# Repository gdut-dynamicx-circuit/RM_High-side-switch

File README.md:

# RM_High-side switch

&nbsp;&nbsp;&nbsp;&nbsp;

[English](./README.md)/中文

***

### 简介

&nbsp;&nbsp;&nbsp;&nbsp;本项目的开发目的是为了实现了电位控制电流。本项目基于lm5060芯片，实现了控制大电流开关的功能。

***

### 开发工具

+ EDA工具：KiCAD 7.0 

***

### 目录结构

+ circuit：基于KiCAD的原理图及PCB设计

+ docs：README相关的图片及文档

**注意：生产制造相关的Gerber、BOM、POS文件及程序固件均在仓库的Release中发布**

***

### 电路设计

#### 原理图设计要点

&nbsp;&nbsp;&nbsp;&nbsp;高侧开关的设计：通过三极管的共射放大电路，实现电位控制Nmos管的导通。在lm5060后面还接入一个可以放电源正负极反接作用的电路。在lm5060的GATE的引脚处串联了一个电阻再反并一个二极管和实现电源快开慢关的作用。

#### PCB布局布线要点

1. VIN旁路电容器靠近引脚VIN.
2. 计时器电容器靠近针脚TIMER.
3. MOS管处pcb打孔确保正反面导通

***

**组织：DynamicX <br>
维护人：陈晓根, 2383725658@qq.com**

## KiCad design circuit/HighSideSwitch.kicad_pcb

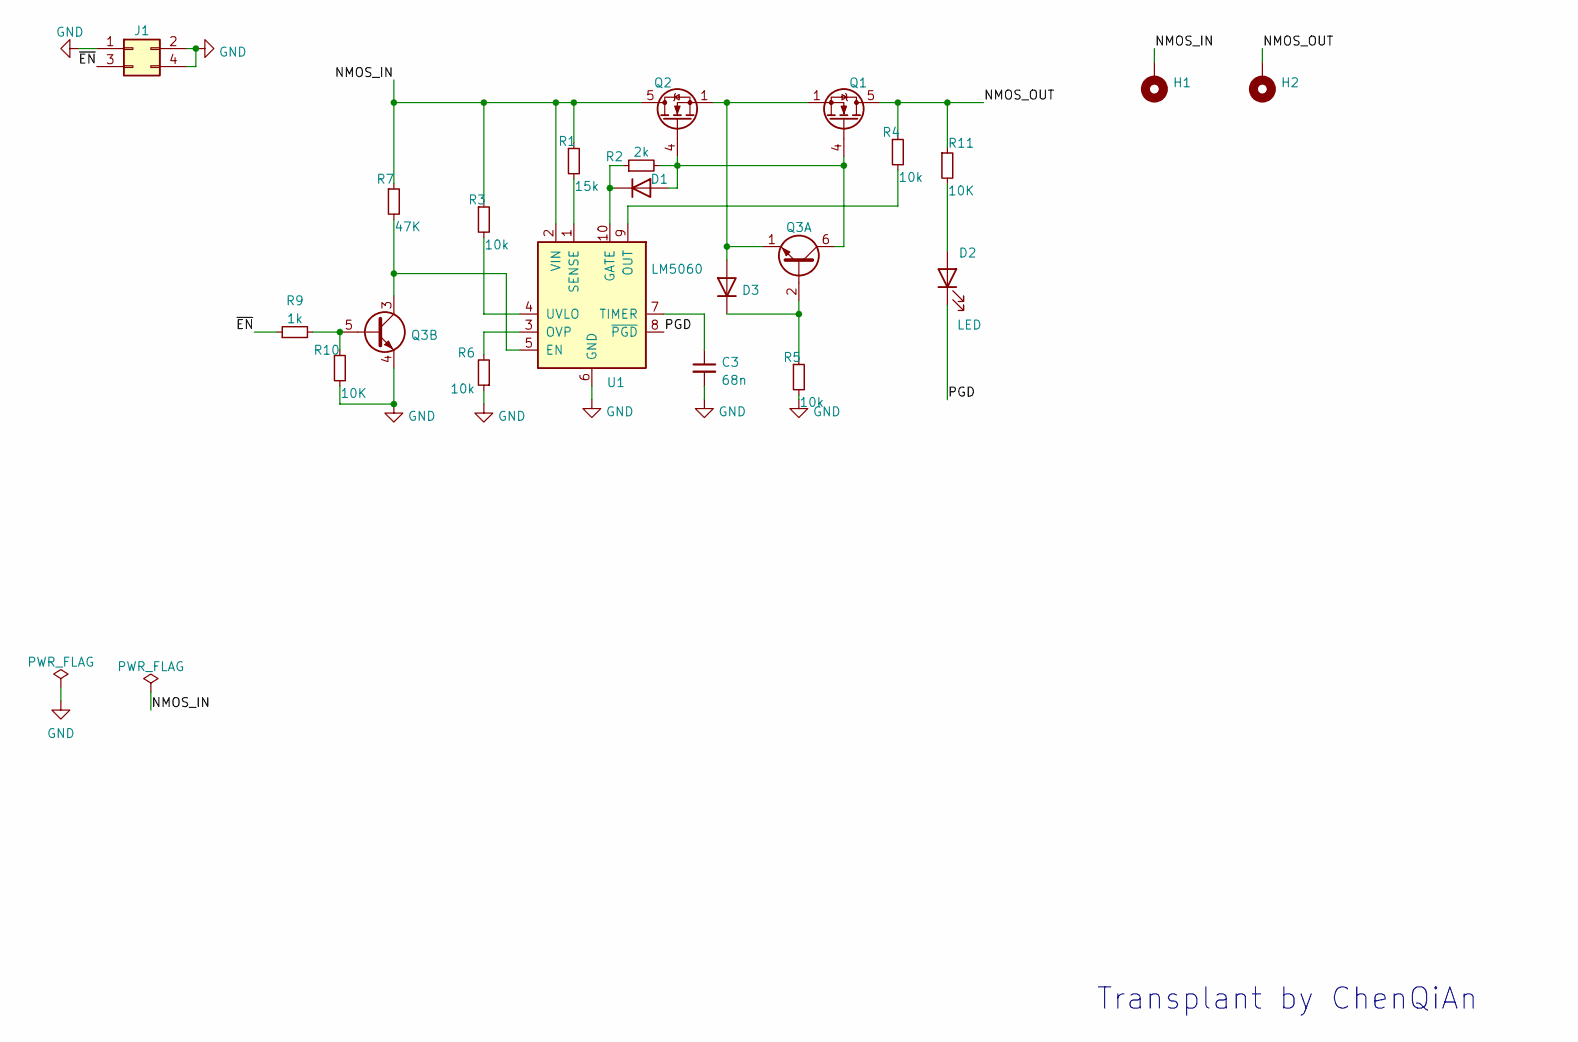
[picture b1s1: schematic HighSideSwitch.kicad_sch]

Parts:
C3: 68n; C_0402_1005Metric
D1, D3: 1N4001; D_SOD-323
D2: LED; LED_0603_1608Metric
H1, H2: MountingHole_Pad; MountingHole_3.2mm_M3_Pad_Via
J1: Conn_02x02_Odd_Even; PinHeader_2x02_P1.27mm_Vertical_SMD
Q1, Q2: CSD18540Q5B; TDSON-8-1
Q3: Q_Dual_NPN_NPN_E1B1C2E2B2C1; SOT-363_SC-70-6
R1: 15k; R_0402_1005Metric
R2: 2k; R_0402_1005Metric
R3, R4, R5, R6: 10k; R_0402_1005Metric
R7: 47K; R_0402_1005Metric
R9: 1k; R_0402_1005Metric
R10, R11: 10K; R_0402_1005Metric
U1: LM5060; MSOP-10_3x3mm_P0.5mm

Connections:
/NMOS_IN: H1.1, Q2.5 (D), R1.1, R3.1, R7.1, U1.2 (VIN)
/NMOS_OUT: H2.1, Q1.5 (D), R4.1, R11.1
/PGD: D2.1 (K), U1.8 (~PGD)
/~EN: J1.3, R9.1
GND: C3.2, J1.1, J1.2, J1.4, Q3.4 (E2), R5.2, R6.1, R10.2, U1.6 (GND)
unnamed: C3.1, U1.7 (TIMER)
unnamed: D1.1 (K), R2.1, U1.10 (GATE)
unnamed: D1.2 (A), Q1.4 (G), Q2.4 (G), Q3.6 (C1), R2.2
unnamed: D2.2 (A), R11.2
unnamed: D3.1 (K), Q3.2 (B1), R5.1
unnamed: D3.2 (A), Q1.1 (S), Q1.2 (S), Q1.3 (S), Q2.1 (S), Q2.2 (S), Q2.3 (S), Q3.1 (E1)
unnamed: Q3.3 (C2), R7.2, U1.5 (EN)
unnamed: Q3.5 (B2), R9.2, R10.1
unnamed: R1.2, U1.1 (SENSE)
unnamed: R3.2, U1.4 (UVLO)
unnamed: R4.2, U1.9 (OUT)
unnamed: R6.2, U1.3 (OVP)

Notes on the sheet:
Transplant by ChenQiAn

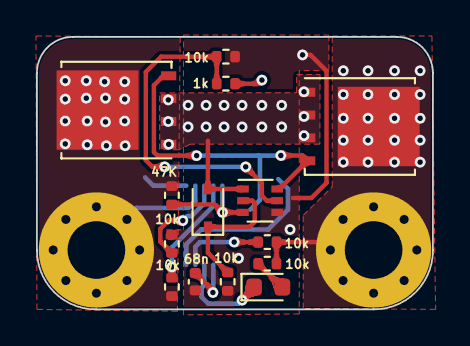
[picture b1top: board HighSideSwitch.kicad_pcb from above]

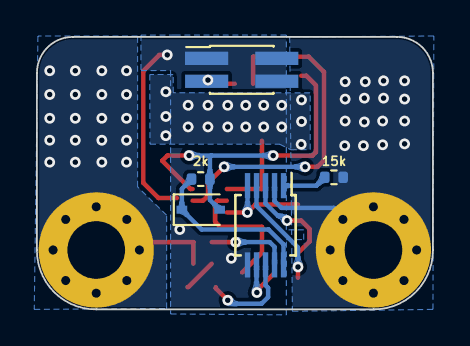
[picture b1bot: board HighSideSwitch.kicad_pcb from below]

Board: 2 copper layers, 22.0 x 15.1 mm, 21 parts (5 on the bottom side), 17 nets.

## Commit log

2023-09-14 first
2023-09-14 second
2023-09-17 Add LICENSE.
2023-09-17 修改了图片的显示问题“

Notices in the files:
README.md:
License: AGPL
